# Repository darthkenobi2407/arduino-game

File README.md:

# arduino-game
a simple console using an arduino nano , buttons and an lcd screen !!
this is a simple game console using an arduino nano , 128x64 oled display and a couple of buttons, currently it has 2 games whihc are like flappy bird and crossy road but more features coming soon like a pause menu a home menu , difficulty and also sound using a simple piezo buzzer , high scores and even some basic animations 
enjoy! :)

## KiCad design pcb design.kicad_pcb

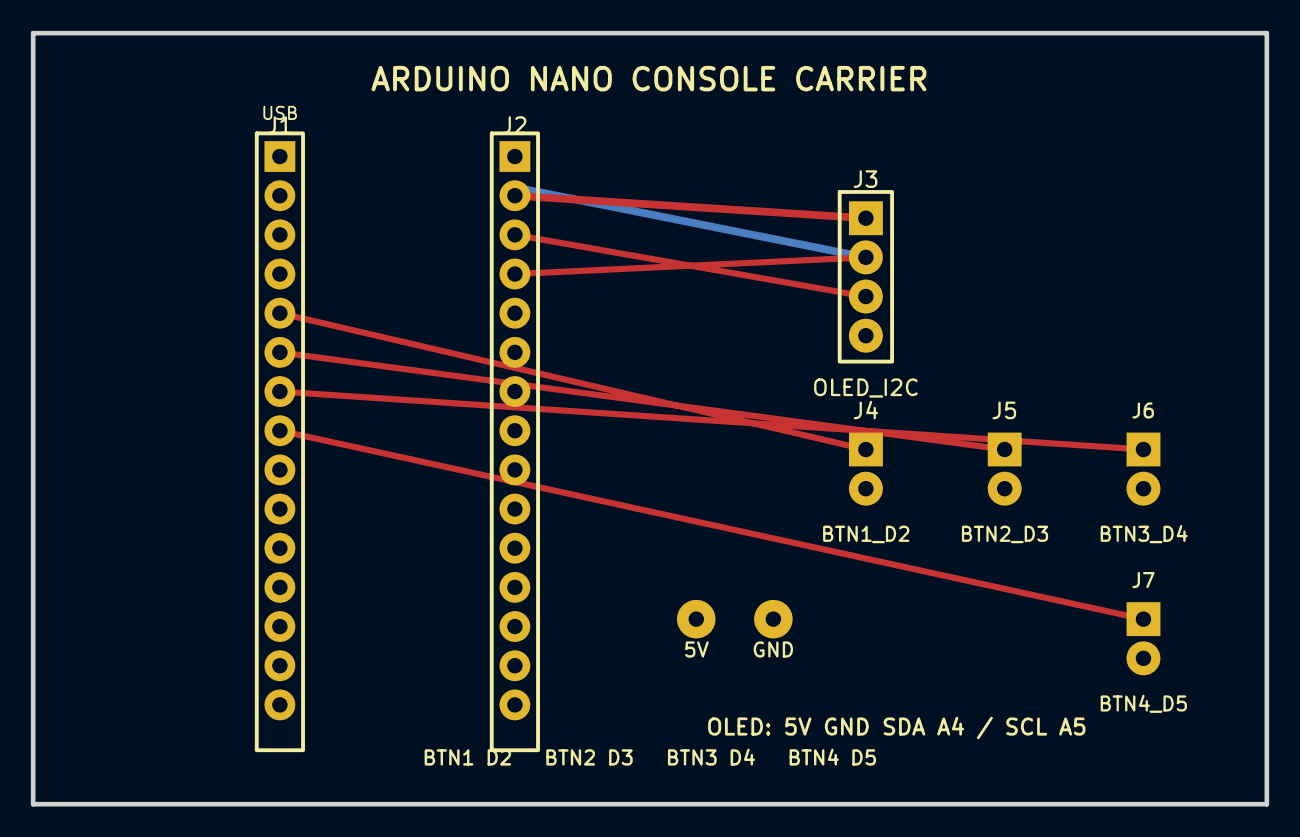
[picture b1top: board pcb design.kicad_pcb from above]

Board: 2 copper layers, 80.0 x 50.0 mm, 9 parts (0 on the bottom side), 8 nets.

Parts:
J1: NANO_LEFT_15PIN; Nano_Header_Left
J2: NANO_RIGHT_15PIN; Nano_Header_Right
J3: OLED_I2C; Connector_PinHeader_1x04
J4: BTN1_D2; Connector_PinHeader_1x02
J5: BTN2_D3; Connector_PinHeader_1x02
J6: BTN3_D4; Connector_PinHeader_1x02
J7: BTN4_D5; Connector_PinHeader_1x02
TP1: 5V; TestPoint
TP2: GND; TestPoint

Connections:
5V: J2.3, J3.1, TP1.1
A4_SDA: J2.7, J3.3
A5_SCL: J2.6, J3.4
D2: J1.5, J4.1
D3: J1.6, J5.1
D4: J1.7, J6.1
D5: J1.8, J7.1
GND: J1.4, J2.2, J3.2, J4.2, J5.2, J6.2, J7.2, TP2.1
